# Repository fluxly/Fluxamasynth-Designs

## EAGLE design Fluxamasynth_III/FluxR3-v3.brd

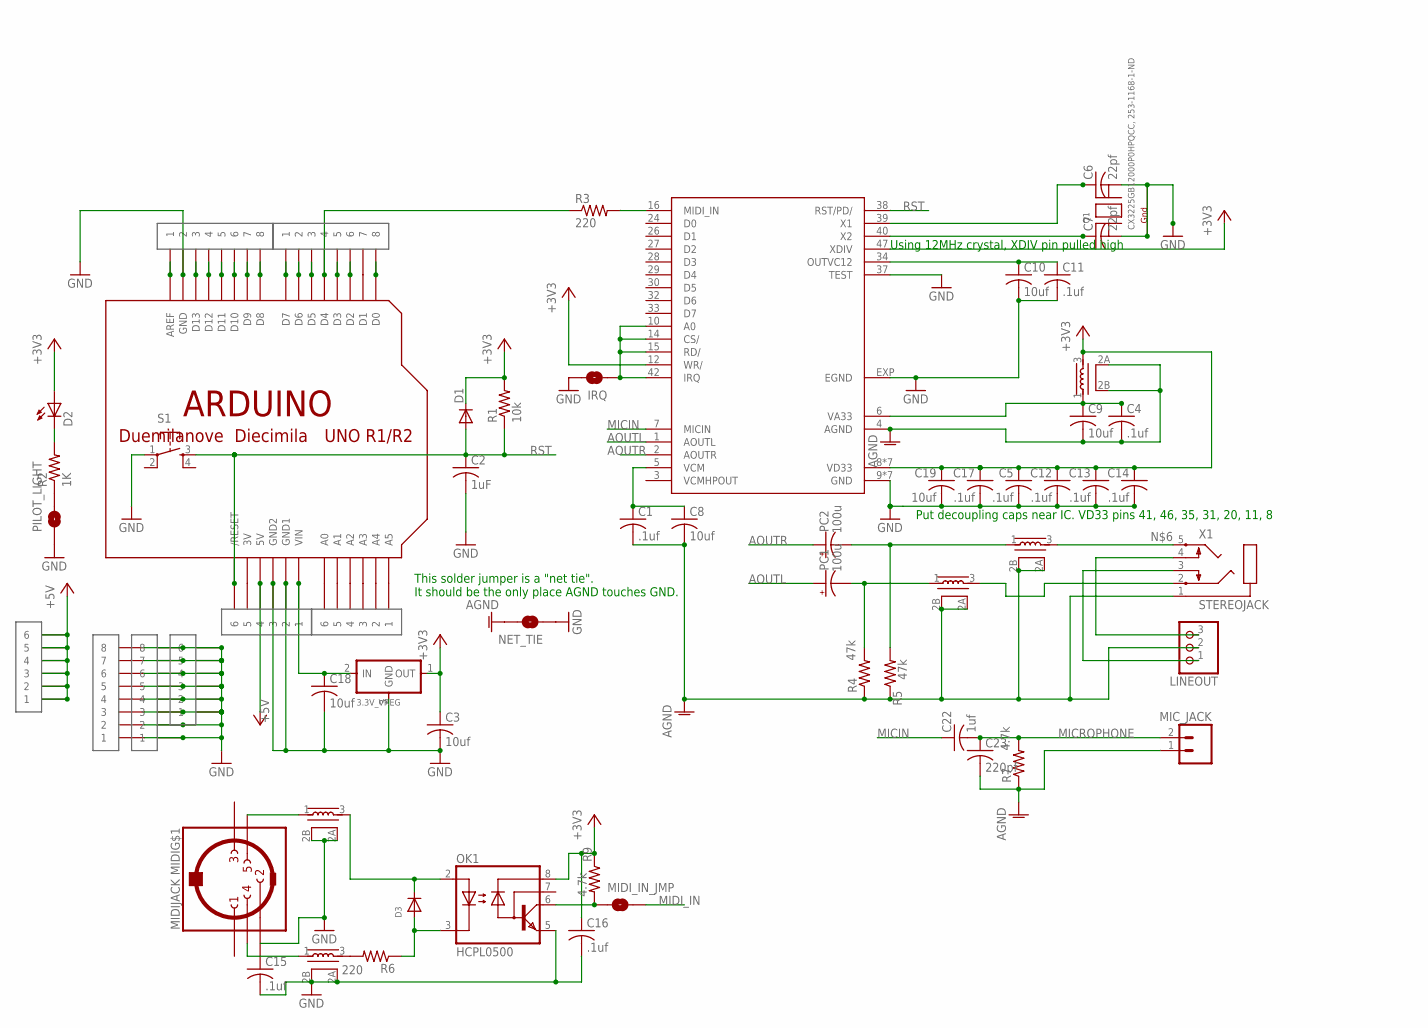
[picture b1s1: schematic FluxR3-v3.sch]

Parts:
3.3V_VREG: REGULATORSOT23; SOT23
ARDUINO: ARDUINO-NOHOLE
C1, C4, C5, C11, C12, C13, C14, C17: .1uf; C0603K
C2: 1uF; C0805
C3, C8, C9, C10, C18, C19: 10uf; C0805
C6, C7: 22pf; C0805
C15, C16: .1uf; C0805
C22: 1uf; C0805
C23: 220pf; C0805
D1: DIODESOD123; SOD123
D2: LED1206; LED-1206
D3: DIODE_SOD-523; SOD-523
IRQ: MODERNDEVICE_SOLDERJUMPERTRACE; MODERNDEVICE_SJ_2S-TRACE
LINEOUT: PINHD-1X3; 1X03
MIC_JACK: M02PTH; 1X02
MIDI: MIDIJACK; CP-2350
MIDI_IN_JMP: SOLDERJUMPERNO; SJ_2S-NO
NET_TIE: MODERNDEVICE_SOLDERJUMPERTRACE; MODERNDEVICE_SJ_2S-TRACE
OK1: HCPL0500; SOIC08
PC1, PC2: 100u; PANASONIC_E
PILOT_LIGHT: MODERNDEVICE_SOLDERJUMPERTRACE; MODERNDEVICE_SJ_2S-TRACE
Q1: CX3225GB12000P0HPQCC, 253-1168-1-ND; MODERNDEVICE_NX3225
R1: 10k; M0805
R2: 1K; M0805
R3, R6: 220; M0805
R4, R5: 47k; R0603
R7: 4.7k; M0805
R9: 4.7k; R0603
S1: 6MM_SWITCH6MM_SWITCH; 6MM_SWITCH
SAM2695: SAM2695; QFN48
U$1, U$9, U$11, U$13: 1X8_CLEAN
U$2, U$3, U$6, U$8: 1X6_CLEAN
U$4, U$5, U$7, U$10, U$12: NFM21CC223R1H3D; 3PC
X1: STEREOJACK; STX3100

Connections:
+3V3: 3.3V_VREG.1 (OUT), C3.1, C5.1, C12.1, C13.1, C14.1, C16.1, C17.1, C19.1, D1.CATHODE (C), D2.A, OK1.8 (VCC), R1.2, R9.1, SAM2695.8 (VD33), SAM2695.11 (VD33), SAM2695.12 (WR/), SAM2695.20 (VD33), SAM2695.31 (VD33), SAM2695.35 (VD33), SAM2695.41 (VD33), SAM2695.46 (VD33), SAM2695.47 (XDIV), U$7.3
+5V: ARDUINO.5V, U$2.P$1 (1), U$2.P$2 (2), U$2.P$3 (3), U$2.P$4 (4), U$2.P$5 (5), U$2.P$6 (6), U$6.P$4 (4)
A0: ARDUINO.A0, U$8.P$6 (6)
A1: ARDUINO.A1, U$8.P$5 (5)
A2: ARDUINO.A2, U$8.P$4 (4)
A3: ARDUINO.A3, U$8.P$3 (3)
A4: ARDUINO.A4, U$8.P$2 (2)
A5: ARDUINO.A5, U$8.P$1 (1)
AGND: C1.2, C4.2, C8.2, C9.2, C23.2, LINEOUT.2, MIC_JACK.1, NET_TIE.2, R4.1, R5.1, R7.1, SAM2695.4 (AGND), U$4.2A, U$4.2B, U$5.2A, U$5.2B, U$7.2A, U$7.2B, X1.1
AOUTL: PC1.+, SAM2695.1 (AOUTL)
AOUTR: PC2.+, SAM2695.2 (AOUTR)
GND: 3.3V_VREG.3 (GND), ARDUINO.GND, ARDUINO.GND1, ARDUINO.GND2, C2.2, C3.2, C5.2, C6.2, C7.2, C10.2, C11.2, C12.2, C13.2, C14.2, C15.2, C16.2, C17.2, C18.2, C19.2, IRQ.2, NET_TIE.1, OK1.5 (GND), PILOT_LIGHT.1, Q1.2 (G2), Q1.4 (G1), S1.1, SAM2695.9 (GND), SAM2695.13 (GND), SAM2695.18 (GND), SAM2695.25 (GND), SAM2695.36 (GND), SAM2695.37 (TEST), SAM2695.45 (GND), SAM2695.48 (GND), SAM2695.EXP (EGND), U$1.P$1 (1), U$1.P$2 (2), U$1.P$3 (3), U$1.P$4 (4), U$1.P$5 (5), U$1.P$6 (6), U$1.P$7 (7), U$1.P$8 (8), U$3.P$1 (1), U$3.P$2 (2), U$3.P$3 (3), U$3.P$4 (4), U$3.P$5 (5), U$3.P$6 (6), U$6.P$2 (2), U$6.P$3 (3), U$10.2A, U$10.2B, U$11.P$1 (1), U$11.P$2 (2), U$11.P$3 (3), U$11.P$4 (4), U$11.P$5 (5), U$11.P$6 (6), U$11.P$7 (7), U$11.P$8 (8), U$12.2A, U$12.2B, U$13.P$2 (2)
MICIN: C22.1, SAM2695.7 (MICIN)
MICROPHONE: C22.2, C23.1, MIC_JACK.2, R7.2
MIDI_FROM_ARDUINO: ARDUINO.D4, MIDI_IN_JMP.1, OK1.6 (VO), R3.1, R9.2, U$9.P$4 (4)
MIDI_IN: MIDI_IN_JMP.2, R3.2, SAM2695.16 (MIDI_IN)
unnamed: ARDUINO.D1, U$9.P$7 (7)
unnamed: MIDI.4, U$10.1
unnamed: IRQ.1, SAM2695.10 (A0), SAM2695.14 (CS/), SAM2695.15 (RD/), SAM2695.42 (IRQ)
unnamed: ARDUINO.3V, U$6.P$5 (5)
unnamed: PC1.-, R4.2, U$5.1
unnamed: U$4.3, X1.5
unnamed: R6.2, U$10.3
unnamed: D3.K (C), OK1.2 (A), U$12.3
unnamed: D2.C, R2.2
unnamed: C15.1, MIDI.2
unnamed: MIDI.5, U$12.1
unnamed: D3.A, OK1.3 (C), R6.1
unnamed: ARDUINO.D8, U$13.P$8 (8)
unnamed: ARDUINO.D9, U$13.P$7 (7)
unnamed: LINEOUT.3, X1.4
unnamed: ARDUINO.D11, U$13.P$5 (5)
unnamed: ARDUINO.D10, U$13.P$6 (6)
unnamed: LINEOUT.1, X1.3
unnamed: ARDUINO.D12, U$13.P$4 (4)
unnamed: ARDUINO.D13, U$13.P$3 (3)
unnamed: ARDUINO.D6, U$9.P$2 (2)
unnamed: ARDUINO.AREF, U$13.P$1 (1)
unnamed: ARDUINO.D5, U$9.P$3 (3)
unnamed: ARDUINO.D0, U$9.P$8 (8)
unnamed: ARDUINO.D2, U$9.P$6 (6)
unnamed: ARDUINO.D3, U$9.P$5 (5)
unnamed: ARDUINO.D7, U$9.P$1 (1)
unnamed: PILOT_LIGHT.2, R2.1
unnamed: C6.1, SAM2695.39 (X1)
unnamed: C7.1, SAM2695.40 (X2)
OUTVC12: C10.1, C11.1, SAM2695.34 (OUTVC12)
OUT_L: U$5.3, X1.2
OUT_R: PC2.-, R5.2, U$4.1
RST: ARDUINO.RESET (/RESET), C2.1, D1.ANODE (A), R1.1, S1.3 (S), SAM2695.38 (RST/PD/), U$6.P$6 (6)
VA33: C4.1, C9.1, SAM2695.6 (VA33), U$7.1
VCM: C1.1, C8.1, SAM2695.5 (VCM)
VIN: 3.3V_VREG.2 (IN), ARDUINO.VIN, C18.1, U$6.P$1 (1)

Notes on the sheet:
Using 12MHz crystal, XDIV pin pulled high
Put decoupling caps near IC. VD33 pins 41, 46, 35, 31, 20, 11, 8
This solder jumper is a "net tie". It should be the only place AGND touches GND.

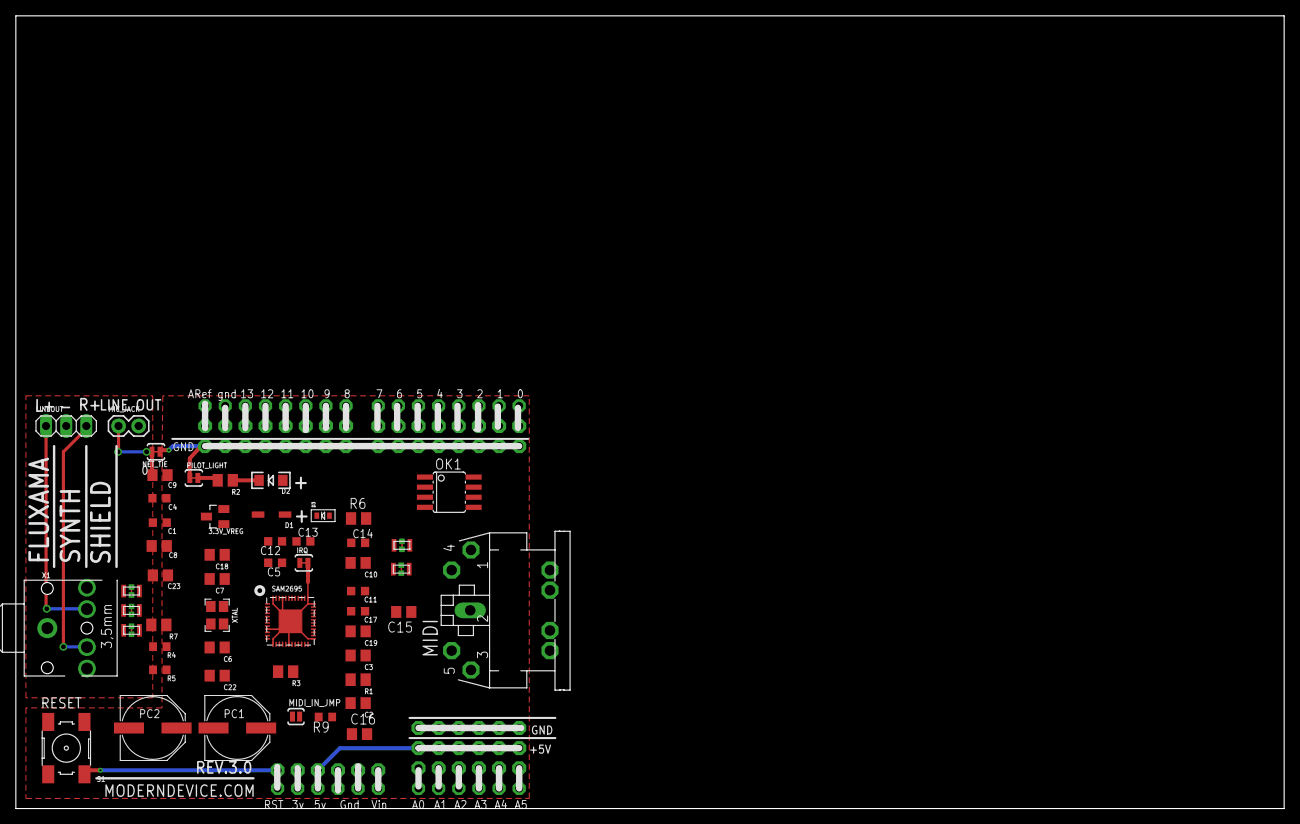
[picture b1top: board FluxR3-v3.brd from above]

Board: 2 copper layers, 160.0 x 100.0 mm, 61 parts (0 on the bottom side), 53 nets.

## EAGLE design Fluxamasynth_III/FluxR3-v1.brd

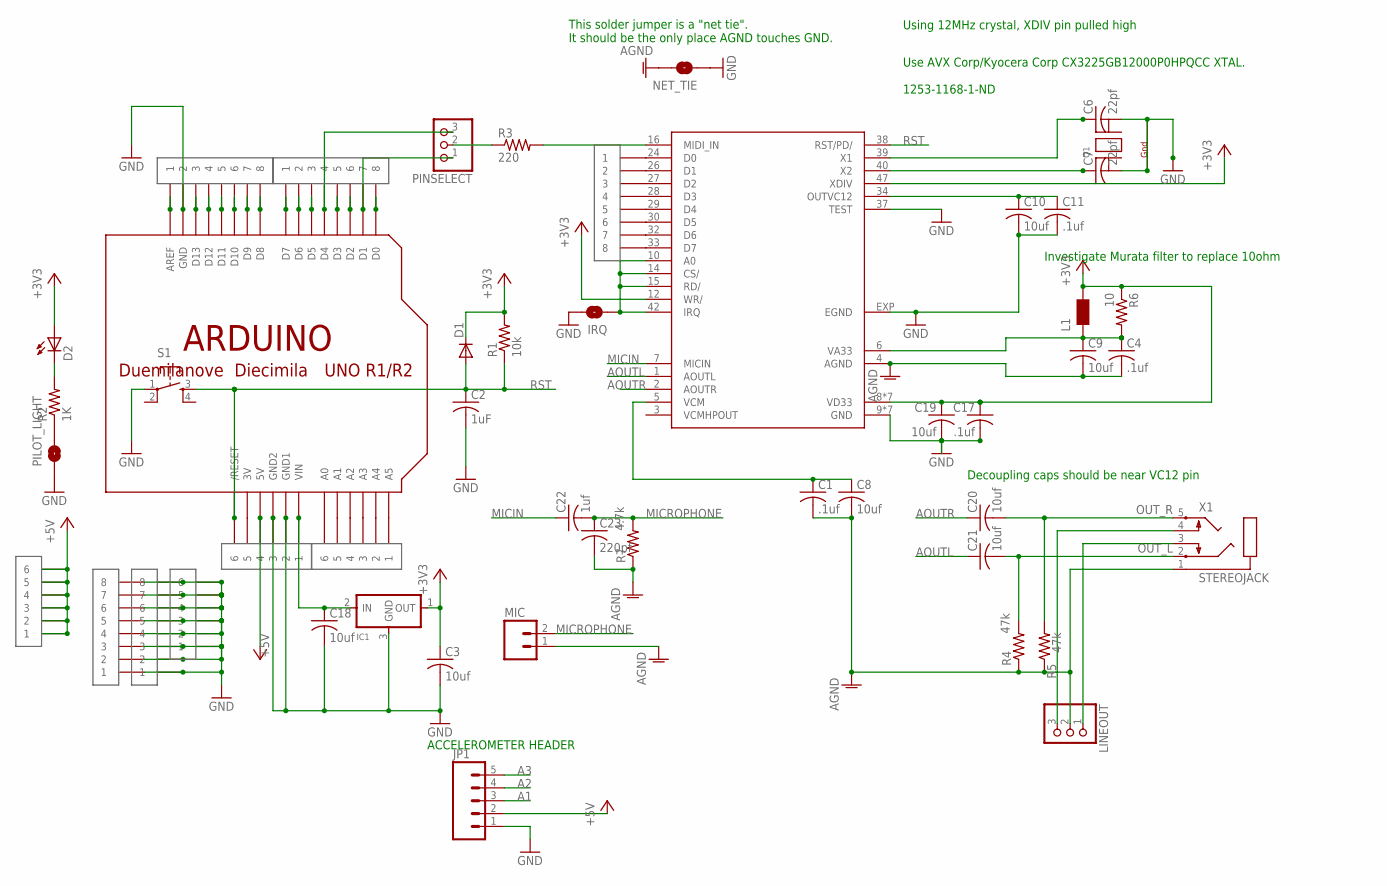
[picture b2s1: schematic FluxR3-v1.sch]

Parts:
C1, C4, C11, C17: .1uf; C0603K
C2: 1uF; C0805
C3, C8, C9, C10, C18, C19, C20, C21: 10uf; C0805
C6, C7: 22pf; C0805
C22: 1uf; C0805
C23: 220pf; C0805
D1: DIODESOD123; SOD123
D2: LED1206; LED-1206
IC1: REGULATORSOT23; SOT23
IRQ: MODERNDEVICE_SOLDERJUMPERTRACE; MODERNDEVICE_SJ_2S-TRACE
JP1: M05NOSILK; 1X05_NOSILK
L1: FERRITE_BEAD_L0603; R0603
LINEOUT: PINHD-1X3; 1X03
MIC: M02PTH; 1X02
MIDI: 1X8_CLEAN
NET_TIE: MODERNDEVICE_SOLDERJUMPERTRACE; MODERNDEVICE_SJ_2S-TRACE
PILOT_LIGHT: MODERNDEVICE_SOLDERJUMPERTRACE; MODERNDEVICE_SJ_2S-TRACE
PINSELECT: PINHD-1X3; 1X03
Q1: MODERNDEVICE_XTAL-4-3225; MODERNDEVICE_NX3225
R1: 10k; M0805
R2: 1K; M0805
R3: 220; M0805
R4, R5: 47k; R0603
R6: 10; M0805
R7: 4.7k; M0805
S1: 6MM_SWITCH6MM_SWITCH; 6MM_SWITCH
U1: SAM2695; QFN48
U$1, U$9, U$11, U$13: 1X8_CLEAN
U$2, U$3, U$6, U$8: 1X6_CLEAN
U$12: ARDUINO-NOHOLE
X1: STEREOJACK; STX3100

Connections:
+3V3: C3.1, C17.1, C19.1, D1.CATHODE (C), D2.A, IC1.1 (OUT), L1.2, R1.2, R6.1, U1.8 (VD33), U1.11 (VD33), U1.12 (WR/), U1.20 (VD33), U1.31 (VD33), U1.35 (VD33), U1.41 (VD33), U1.46 (VD33), U1.47 (XDIV)
+5V: JP1.2, U$2.P$1 (1), U$2.P$2 (2), U$2.P$3 (3), U$2.P$4 (4), U$2.P$5 (5), U$2.P$6 (6), U$6.P$4 (4), U$12.5V
A0: U$8.P$6 (6), U$12.A0
A1: JP1.3, U$8.P$5 (5), U$12.A1
A2: JP1.4, U$8.P$4 (4), U$12.A2
A3: JP1.5, U$8.P$3 (3), U$12.A3
A4: U$8.P$2 (2), U$12.A4
A5: U$8.P$1 (1), U$12.A5
AGND: C1.2, C4.2, C8.2, C9.2, C23.2, LINEOUT.2, MIC.1, NET_TIE.2, R4.1, R5.1, R7.1, U1.4 (AGND), X1.1
AOUTL: C21.1, U1.1 (AOUTL)
AOUTR: C20.1, U1.2 (AOUTR)
GND: C2.2, C3.2, C6.2, C7.2, C10.2, C11.2, C17.2, C18.2, C19.2, IC1.3 (GND), IRQ.2, JP1.1, NET_TIE.1, PILOT_LIGHT.1, Q1.2 (G2), Q1.4 (G1), S1.1, U1.9 (GND), U1.13 (GND), U1.18 (GND), U1.25 (GND), U1.36 (GND), U1.37 (TEST), U1.45 (GND), U1.48 (GND), U1.EXP (EGND), U$1.P$1 (1), U$1.P$2 (2), U$1.P$3 (3), U$1.P$4 (4), U$1.P$5 (5), U$1.P$6 (6), U$1.P$7 (7), U$1.P$8 (8), U$3.P$1 (1), U$3.P$2 (2), U$3.P$3 (3), U$3.P$4 (4), U$3.P$5 (5), U$3.P$6 (6), U$6.P$2 (2), U$6.P$3 (3), U$11.P$1 (1), U$11.P$2 (2), U$11.P$3 (3), U$11.P$4 (4), U$11.P$5 (5), U$11.P$6 (6), U$11.P$7 (7), U$11.P$8 (8), U$12.GND, U$12.GND1, U$12.GND2, U$13.P$2 (2)
MICIN: C22.1, U1.7 (MICIN)
MICROPHONE: C22.2, C23.1, MIC.2, R7.2
unnamed: PINSELECT.2, R3.1
unnamed: R3.2, U1.16 (MIDI_IN)
unnamed: IRQ.1, U1.10 (A0), U1.14 (CS/), U1.15 (RD/), U1.42 (IRQ)
unnamed: U$6.P$5 (5), U$12.3V
unnamed: MIDI.P$1 (1), U1.24 (D0)
unnamed: MIDI.P$2 (2), U1.26 (D1)
unnamed: MIDI.P$3 (3), U1.27 (D2)
unnamed: MIDI.P$4 (4), U1.28 (D3)
unnamed: D2.C, R2.2
unnamed: MIDI.P$5 (5), U1.29 (D4)
unnamed: MIDI.P$6 (6), U1.30 (D5)
unnamed: C1.1, C8.1, U1.5 (VCM)
unnamed: MIDI.P$7 (7), U1.32 (D6)
unnamed: MIDI.P$8 (8), U1.33 (D7)
unnamed: U$12.D8, U$13.P$8 (8)
unnamed: PINSELECT.1, U$9.P$7 (7), U$12.D1
unnamed: PINSELECT.3, U$9.P$4 (4), U$12.D4
unnamed: U$12.D9, U$13.P$7 (7)
unnamed: LINEOUT.3, X1.4
unnamed: U$12.D11, U$13.P$5 (5)
unnamed: U$12.D10, U$13.P$6 (6)
unnamed: LINEOUT.1, X1.3
unnamed: U$12.D12, U$13.P$4 (4)
unnamed: U$12.D13, U$13.P$3 (3)
unnamed: U$9.P$2 (2), U$12.D6
unnamed: U$12.AREF, U$13.P$1 (1)
unnamed: U$9.P$3 (3), U$12.D5
unnamed: U$9.P$8 (8), U$12.D0
unnamed: U$9.P$6 (6), U$12.D2
unnamed: U$9.P$5 (5), U$12.D3
unnamed: U$9.P$1 (1), U$12.D7
unnamed: C4.1, C9.1, L1.1, R6.2, U1.6 (VA33)
unnamed: PILOT_LIGHT.2, R2.1
unnamed: C6.1, U1.39 (X1)
unnamed: C7.1, U1.40 (X2)
OUTVC12: C10.1, C11.1, U1.34 (OUTVC12)
OUT_L: C21.2, R4.2, X1.2
OUT_R: C20.2, R5.2, X1.5
RST: C2.1, D1.ANODE (A), R1.1, S1.3 (S), U1.38 (RST/PD/), U$6.P$6 (6), U$12.RESET (/RESET)
VIN: C18.1, IC1.2 (IN), U$6.P$1 (1), U$12.VIN

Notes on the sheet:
Using 12MHz crystal, XDIV pin pulled high
Investigate Murata filter to replace 10ohm
Use AVX Corp/Kyocera Corp CX3225GB12000P0HPQCC XTAL. 1253-1168-1-ND
Decoupling caps should be near VC12 pin
This solder jumper is a "net tie". It should be the only place AGND touches GND.
ACCELEROMETER HEADER

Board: 2 copper layers, 49 parts (0 on the bottom side), 54 nets, no tracks yet.

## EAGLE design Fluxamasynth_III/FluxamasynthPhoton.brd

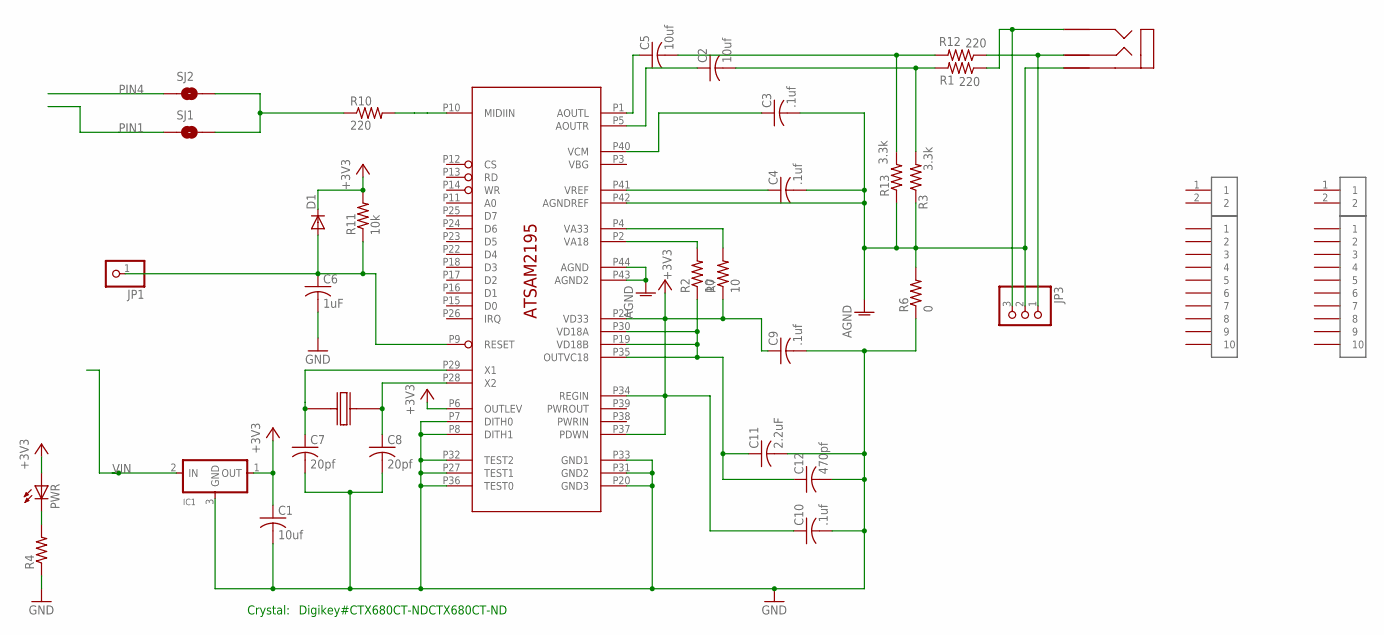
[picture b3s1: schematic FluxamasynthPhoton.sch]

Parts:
C1, C2, C5: 10uf; C0603
C3, C4, C9, C10: .1uf; C0603
C6: 1uF; C0603
C7, C8: 20pf; C0603K
C11: 2.2uF; C0603
C12: 470pf; C0603
D1: DIODESOD123; SOD123
IC1: REGULATORSOT23; SOT23
JP1: PINHD-1X1; 1X01
JP3: PINHD-1X3CB; 1X03-CLEANBIG
PWR: LED0603; LED-0603
R1, R10, R12: 220; R0603
R2, R7: 10; R0603
R3, R13: 3.3k; R0603
R4: R-US_R0603; R0603
R6: 0; R0603
R11: 10k; R0603
SJ1: SOLDERJUMPERNO; SJ_2S-NO
SJ2: SOLDERJUMPERNC2; SJ_2S-NOTRACE
U$1: ATSAM2195
U$2: CRYSTAL_7X5
U$3, U$5: 1X10_CLEAN
U$4: STEREO_AUDIO_JACK_SMT
U$6, U$7: 1X2_CLEAN

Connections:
+3V3: C1.1, C9.1, C10.1, D1.CATHODE (C), IC1.1 (OUT), PWR.A, R7.1, R11.2, U$1.P6 (OUTLEV), U$1.P21 (VD33), U$1.P34 (REGIN), U$1.P37 (PDWN)
AGND: C3.2, C4.2, JP3.2, R3.1, R6.2, R13.1, U$1.P42 (AGNDREF), U$1.P43 (AGND2), U$1.P44 (AGND), U$4.P$1 (SHIELD)
CA11: C2.1, U$1.P5 (AOUTR)
GND: C1.2, C6.2, C7.2, C8.2, C9.2, C10.2, C11.2, C12.2, IC1.3 (GND), R4.1, R6.1, U$1.P7 (DITH0), U$1.P8 (DITH1), U$1.P20 (GND3), U$1.P27 (TEST1), U$1.P31 (GND2), U$1.P32 (TEST2), U$1.P33 (GND1), U$1.P36 (TEST0)
unnamed: R10.1, SJ1.2, SJ2.2
unnamed: R10.2, U$1.P10 (MIDIIN)
unnamed: C8.1, U$1.P28 (X2), U$2.P$3
unnamed: C7.1, U$1.P29 (X1), U$2.P$1
unnamed: C11.1, C12.1, R2.1, U$1.P19 (VD18B), U$1.P30 (VD18A), U$1.P35 (OUTVC18)
unnamed: R2.2, U$1.P2 (VA18)
unnamed: C5.1, U$1.P1 (AOUTL)
unnamed: PWR.C, R4.2
unnamed: C5.2, R12.2, R13.2
unnamed: C2.2, R1.2, R3.2
unnamed: C3.1, U$1.P40 (VCM)
unnamed: R7.2, U$1.P4 (VA33)
unnamed: C6.1, D1.ANODE (A), JP1.1, R11.1, U$1.P9 (RESET)
unnamed: C4.1, U$1.P41 (VREF)
unnamed: JP3.3, R1.1, U$4.P$2 (TIP)
unnamed: JP3.1, R12.1, U$4.P$3 (RING)
PIN1: SJ1.1
PIN4: SJ2.1
VIN: IC1.2 (IN)

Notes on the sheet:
Digikey#CTX680CT-NDCTX680CT-ND
Crystal:

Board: 2 copper layers, 36 parts (1 on the bottom side), 20 nets, no tracks yet.

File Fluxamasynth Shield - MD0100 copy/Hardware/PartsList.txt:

Partlist

Exported from FluxamasynthShield.sch at 12/22/10 11:38 AM

EAGLE Version 5.10.0 Copyright (c) 1988-2010 CadSoft

Part     Value                      Device                     Package        Library             Sheet

C1       10uf                       C-USC0805                  C0805          rcl                 1
C2       2.2uF                      C-USC0805                  C0805          rcl                 1
C3       .1uf                       C-USC0805                  C0805          rcl                 1
C4       .1uf                       C-USC0805                  C0805          rcl                 1
C5       2.2uF                      C-USC0805                  C0805          rcl                 1
C6       1uF                        C-USC0805                  C0805          rcl                 1
C7       18pf                       C-USC0805                  C0805          rcl                 1
C8       18pf                       C-USC0805                  C0805          rcl                 1
C9       .1uf                       C-USC0805                  C0805          rcl                 1
C10      .1uf                       C-USC0805                  C0805          rcl                 1
C11      2.2uF                      C-USC0805                  C0805          rcl                 1
C12      470pf                      C-USC0805                  C0805          rcl                 1
D1                                  DIODESOD123                SOD123         ng                  1
IC1                                 REGULATORSOT23             SOT23          ng                  1
JP1                                 PINHD-1X3                  1X03           pinhead             1
JP3                                 PINHD-1X3                  1X03           pinhead             1
Q2       9.6MHz                     CRYSTALTC26H               TC26H          crystal             1
R1       220                        R-US_M0805                 M0805          rcl                 1
R2       10                         R-US_M0805                 M0805          rcl                 1
R3       3.3k                       R-US_M0805                 M0805          rcl                 1
R4                                  R-US_M0805                 M0805          rcl                 1
R6       0                          R-US_M0805                 M0805          rcl                 1
R7       10                         R-US_M0805                 M0805          rcl                 1
R10      220                        R-US_M0805                 M0805          rcl                 1
R11      10k                        R-US_M0805                 M0805          rcl                 1
R12      220                        R-US_M0805                 M0805          rcl                 1
R13      3.3k                       R-US_M0805                 M0805          rcl                 1
S1                                  6MM_SWITCH6MM_SWITCH       6MM_SWITCH     ng                  1
U$1      ATSAM2195                  ATSAM2195                  ATSAM2195      ATSAM2195           1
U$2      ARDUINODUEMILANOVE-NOHOLES ARDUINODUEMILANOVE-NOHOLES ARDUINO-NOHOLE adafruit            1
U$3                                 LED1206                    1206           ng                  1
U$4      1X6HEADER                  1X6HEADER                  1X6HEADER      ModernDeviceHeaders 1
U$5      1X6HEADER                  1X6HEADER                  1X6HEADER      ModernDeviceHeaders 1
U$6      1X8HEADER                  1X8HEADER                  1X8HEADER      ModernDeviceHeaders 1
U$7      1X8HEADER                  1X8HEADER                  1X8HEADER      ModernDeviceHeaders 1
U$8      1X6HEADER                  1X6HEADER                  1X6HEADER      ModernDeviceHeaders 1
U$9      1X6HEADER                  1X6HEADER                  1X6HEADER      ModernDeviceHeaders 1
U$10     1X8HEADER                  1X8HEADER                  1X8HEADER      ModernDeviceHeaders 1
U$11     1X8HEADER                  1X8HEADER                  1X8HEADER      ModernDeviceHeaders 1
U$12     1X6HEADER                  1X6HEADER                  1X6HEADER      ModernDeviceHeaders 1
U$13     1X6HEADER                  1X6HEADER                  1X6HEADER      ModernDeviceHeaders 1
X1       STEREOJACK                 STEREOJACK                 STX3100        adafruit            1

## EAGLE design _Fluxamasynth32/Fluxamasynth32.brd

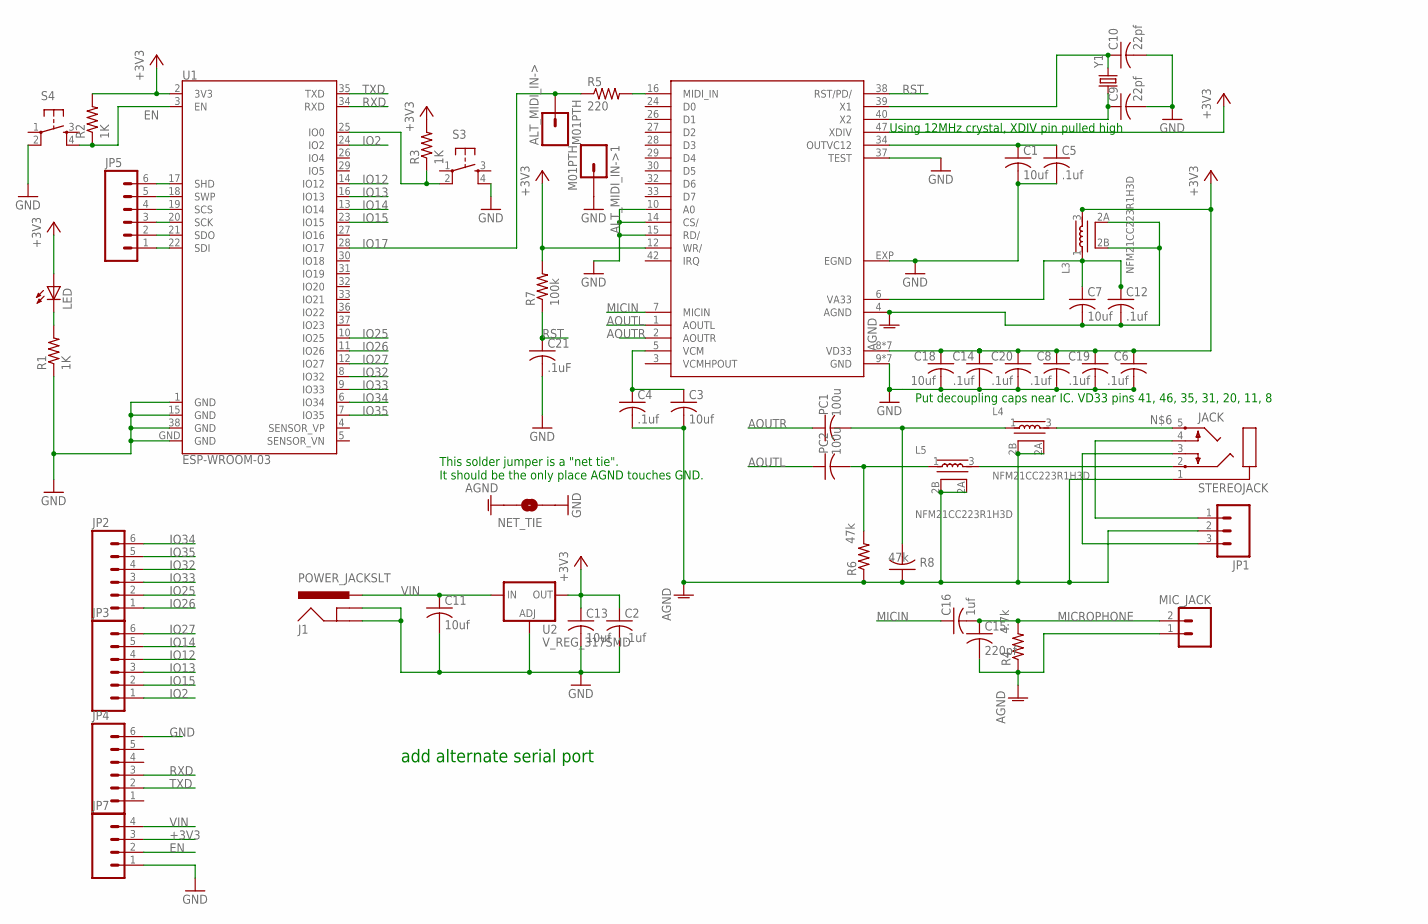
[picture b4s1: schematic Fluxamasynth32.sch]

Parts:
ALT_MIDI_IN->, ALT_MIDI_IN->1: M01PTH; 1X01
C1, C3, C7: 10uf; C0805K
C2, C4, C5, C6, C8, C12, C14, C19, C20: .1uf; C0603K
C9, C10: 22pf; C0603
C11, C13: 10uf; C1206
C15: 220pf; C0805K
C16: 1uf; C0603K
C18: 10uf; C0603K
C21: .1uF; C0603K
J1: POWER_JACKSLT; POWER_JACK_SLOT
JACK: STEREOJACK; STX3100
JP1: M03PTH; 1X03
JP2, JP3, JP4, JP5: M06NO_SILK; 1X06_NO_SILK
JP7: M041X04_NO_SILK; 1X04_NO_SILK
L3, L4, L5: NFM21CC223R1H3D; 3PC
LED: LED0603; LED-0603
MIC_JACK: M02PTH; 1X02
NET_TIE: MODERNDEVICE_SOLDERJUMPERTRACE; MODERNDEVICE_SJ_2S-TRACE
PC1, PC2: 100u; C1206K
R1, R2, R3: 1K; R0603
R4: 4.7k; R0603
R5: 220; R0603
R6: 47k; R0603
R7: 100k; R0603
R8: 47k; C0603K
S3, S4: 6MM_SWITCH6MM_SWITCH; 6MM_SWITCH
SAM2695: SAM2695; QFN48
U1: ESP-WROOM-03
U2: V_REG_317SMD; SOT223
Y1: CRYSTALTXC-7A; CRYSTAL-TXC-7A

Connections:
+3V3: C2.1, C6.1, C8.1, C13.1, C14.1, C18.1, C19.1, C20.1, JP7.3, L3.3, LED.A, R2.2, R3.2, R7.2, SAM2695.8 (VD33), SAM2695.11 (VD33), SAM2695.12 (WR/), SAM2695.20 (VD33), SAM2695.31 (VD33), SAM2695.35 (VD33), SAM2695.41 (VD33), SAM2695.46 (VD33), SAM2695.47 (XDIV), U1.2 (3V3), U2.2 (OUT), U2.4 (OUT)
AGND: C3.2, C4.2, C7.2, C12.2, C15.2, JACK.1, JP1.2, L3.2A, L3.2B, L4.2A, L4.2B, L5.2A, L5.2B, MIC_JACK.1, NET_TIE.2, R4.1, R6.1, R8.1, SAM2695.4 (AGND)
AOUTL: PC2.1, SAM2695.1 (AOUTL)
AOUTR: PC1.1, SAM2695.2 (AOUTR)
EN: JP7.2, R2.1, S4.4 (S1), U1.3 (EN)
GND: ALT_MIDI_IN->1.1, C1.2, C2.2, C5.2, C6.2, C8.2, C9.2, C10.2, C11.2, C13.2, C14.2, C18.2, C19.2, C20.2, C21.2, J1.GND@1 (GNDBREAK), J1.GND@2 (GND), JP4.6, JP7.1, NET_TIE.1, R1.1, S3.4 (S1), S4.2 (P1), SAM2695.9 (GND), SAM2695.10 (A0), SAM2695.13 (GND), SAM2695.14 (CS/), SAM2695.15 (RD/), SAM2695.18 (GND), SAM2695.25 (GND), SAM2695.36 (GND), SAM2695.37 (TEST), SAM2695.45 (GND), SAM2695.48 (GND), SAM2695.EXP (EGND), U1.1 (GND), U1.15 (GND), U1.38 (GND), U1.GND, U2.1 (ADJ)
IO2: JP3.1, U1.24 (IO2)
IO12: JP3.4, U1.14 (IO12)
IO13: JP3.3, U1.16 (IO13)
IO14: JP3.5, U1.13 (IO14)
IO15: JP3.2, U1.23 (IO15)
IO17: ALT_MIDI_IN->.1, R5.1, U1.28 (IO17)
IO25: JP2.2, U1.10 (IO25)
IO26: JP2.1, U1.11 (IO26)
IO27: JP3.6, U1.12 (IO27)
IO32: JP2.4, U1.8 (IO32)
IO33: JP2.3, U1.9 (IO33)
IO34: JP2.6, U1.6 (IO34)
IO35: JP2.5, U1.7 (IO35)
MICIN: C16.1, SAM2695.7 (MICIN)
MICROPHONE: C15.1, C16.2, MIC_JACK.2, R4.2
unnamed: R3.1, S3.2 (P1), U1.25 (IO0)
unnamed: JP5.1, U1.22 (SDI)
unnamed: L5.1, PC2.2, R6.2
unnamed: JACK.5, L4.3
unnamed: JP5.2, U1.21 (SDO)
unnamed: JP5.3, U1.20 (SCK)
unnamed: LED.C, R1.2
unnamed: JP5.4, U1.19 (SCS)
unnamed: JP5.5, U1.18 (SWP)
unnamed: R5.2, SAM2695.16 (MIDI_IN)
unnamed: JP5.6, U1.17 (SHD)
unnamed: JACK.4, JP1.1
unnamed: JACK.3, JP1.3
OUTVC12: C1.1, C5.1, SAM2695.34 (OUTVC12)
OUT_L: JACK.2, L5.3
OUT_R: L4.1, PC1.2, R8.2
RST: C21.1, R7.1, SAM2695.38 (RST/PD/)
RXD: JP4.3, U1.34 (RXD)
TXD: JP4.2, U1.35 (TXD)
VA33: C7.1, C12.1, L3.1, SAM2695.6 (VA33)
VCM: C3.1, C4.1, SAM2695.5 (VCM)
VIN: C11.1, J1.PWR, JP7.4, U2.3 (IN)
XTL1: C10.1, SAM2695.39 (X1), Y1.P$2 (2)
XTL2: C9.1, SAM2695.40 (X2), Y1.P$1 (1)

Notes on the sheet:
Using 12MHz crystal, XDIV pin pulled high
Put decoupling caps near IC. VD33 pins 41, 46, 35, 31, 20, 11, 8
This solder jumper is a "net tie". It should be the only place AGND touches GND.
add alternate serial port

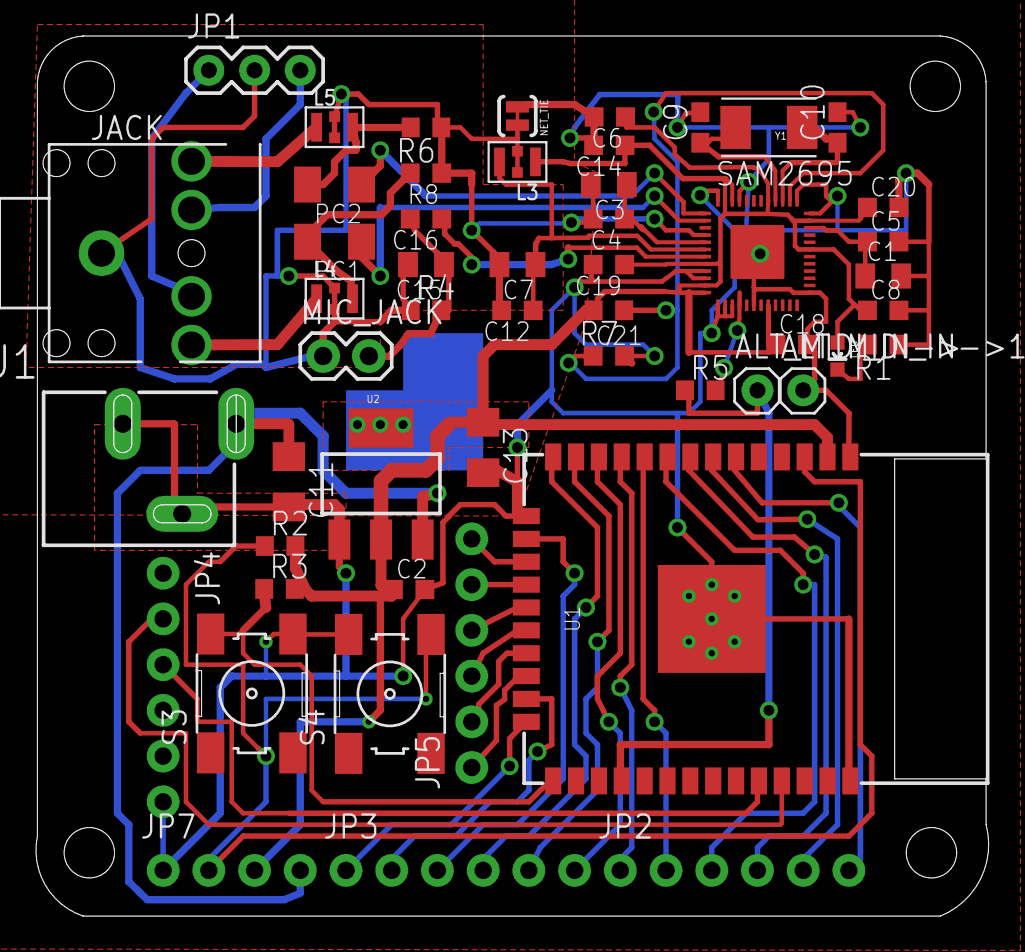
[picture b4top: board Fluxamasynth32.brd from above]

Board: 2 copper layers, 52.9 x 48.9 mm, 52 parts (0 on the bottom side), 45 nets.

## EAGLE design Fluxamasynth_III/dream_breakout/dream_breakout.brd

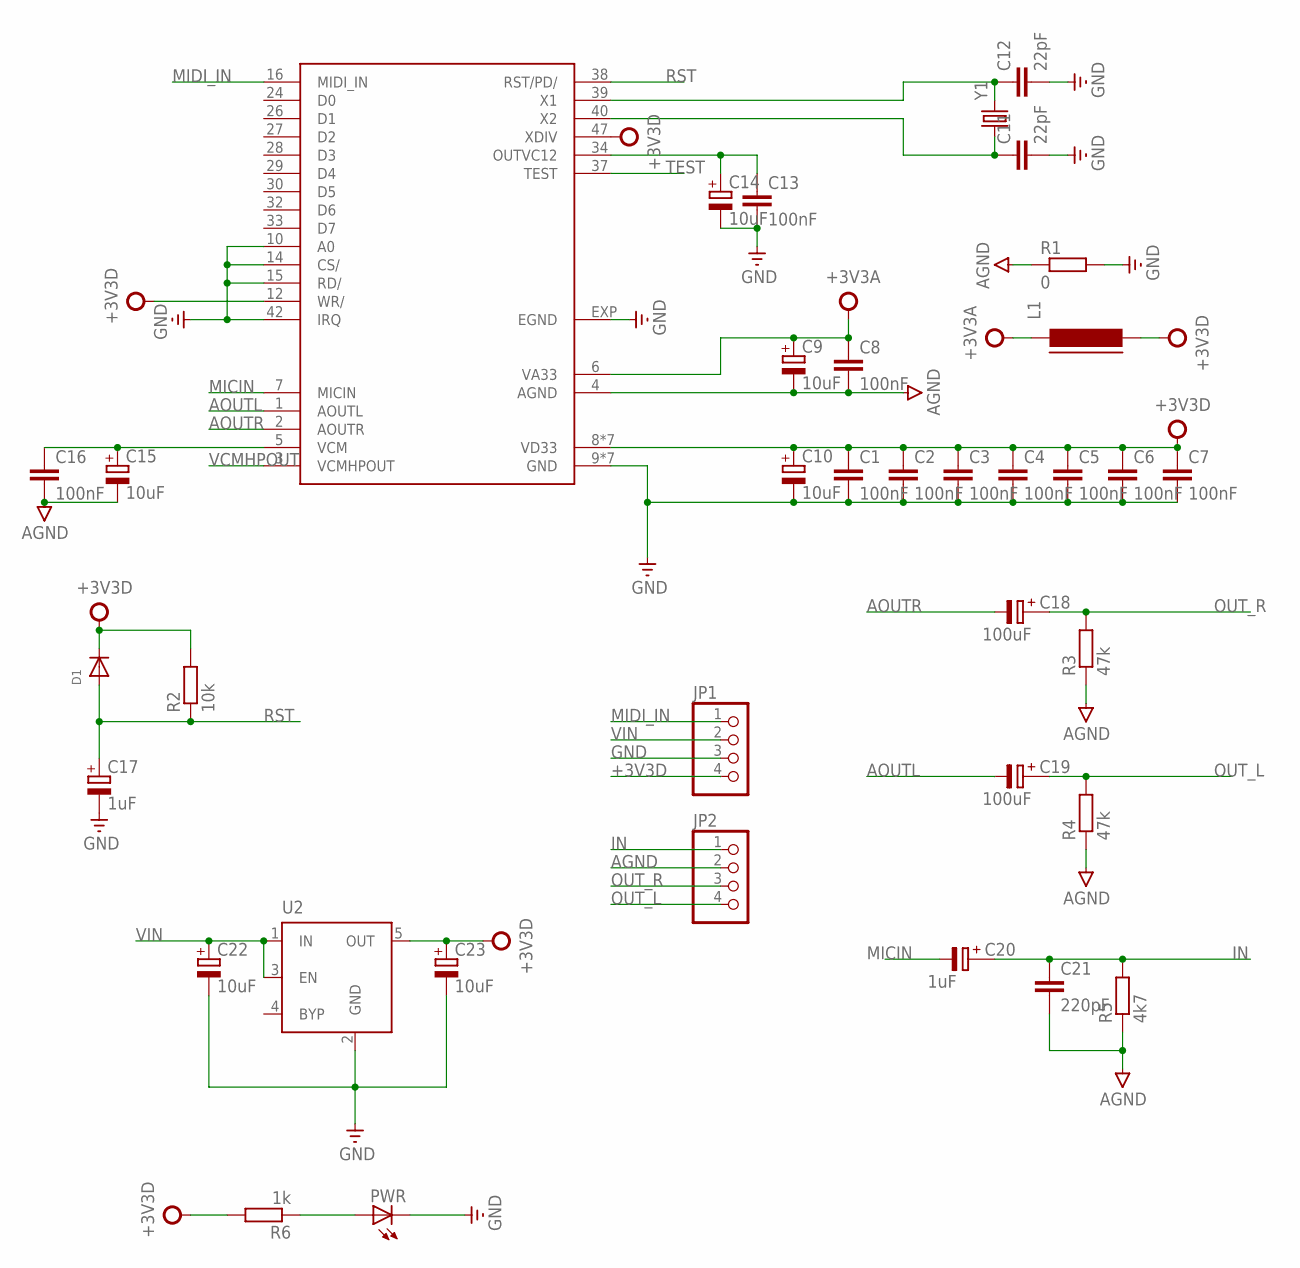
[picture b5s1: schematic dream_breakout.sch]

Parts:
C1, C2, C3, C4, C5, C6, C7, C8, C13, C16: 100nF; C0603K
C9, C10, C14, C15, C22, C23: 10uF; A/3216-18R
C11, C12: 22pF; C0603K
C17: 1uF; A/3216-18R
C18, C19: 100uF; SV-B
C20: 1uF; SV-B
C21: 220pF; C0603K
D1: DIODESOD-123; SOD-123
JP1, JP2: HEADER-1X4ROUND; 1X04_ROUND
L1: FERRITE-0603; FB603
PWR: LEDCHIP-LED0603; CHIP-LED0603
R1: 0; R0603
R2: 10k; R0603
R3, R4: 47k; R0603
R5: 4k7; R0603
R6: 1k; R0603
U1: SAM2695; QFN48
U2: MIC5219XX; SOT23-5
Y1: CRYSTALTXC-7A; CRYSTAL-TXC-7A

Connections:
+3V3A: C8.1, C9.+, L1.1, U1.6 (VA33)
+3V3D: C1.1, C2.1, C3.1, C4.1, C5.1, C6.1, C7.1, C10.+, C23.+, D1.C, JP1.4, L1.2, R2.2, R6.2, U1.8 (VD33), U1.11 (VD33), U1.12 (WR/), U1.20 (VD33), U1.31 (VD33), U1.35 (VD33), U1.41 (VD33), U1.46 (VD33), U1.47 (XDIV), U2.5 (OUT)
AGND: C8.2, C9.-, C15.-, C16.2, C21.2, JP2.2, R1.1, R3.1, R4.1, R5.1, U1.4 (AGND)
AOUTL: C19.-, U1.1 (AOUTL)
AOUTR: C18.-, U1.2 (AOUTR)
GND: C1.2, C2.2, C3.2, C4.2, C5.2, C6.2, C7.2, C10.-, C11.2, C12.2, C13.2, C14.-, C17.-, C22.-, C23.-, JP1.3, PWR.C, R1.2, U1.9 (GND), U1.10 (A0), U1.13 (GND), U1.14 (CS/), U1.15 (RD/), U1.18 (GND), U1.25 (GND), U1.36 (GND), U1.42 (IRQ), U1.45 (GND), U1.48 (GND), U1.EXP (EGND), U2.2 (GND)
IN: C20.+, C21.1, JP2.1, R5.2
MICIN: C20.-, U1.7 (MICIN)
MIDI_IN: JP1.1, U1.16 (MIDI_IN)
unnamed: C13.1, C14.+, U1.34 (OUTVC12)
unnamed: C12.1, U1.39 (X1), Y1.P$2 (2)
unnamed: C11.1, U1.40 (X2), Y1.P$1 (1)
unnamed: PWR.A, R6.1
unnamed: C15.+, C16.1, U1.5 (VCM)
OUT_L: C19.+, JP2.4, R4.2
OUT_R: C18.+, JP2.3, R3.2
RST: C17.+, D1.A, R2.1, U1.38 (RST/PD/)
TEST: U1.37 (TEST)
VCMHPOUT: U1.3 (VCMHPOUT)
VIN: C22.+, JP1.2, U2.1 (IN), U2.3 (EN)

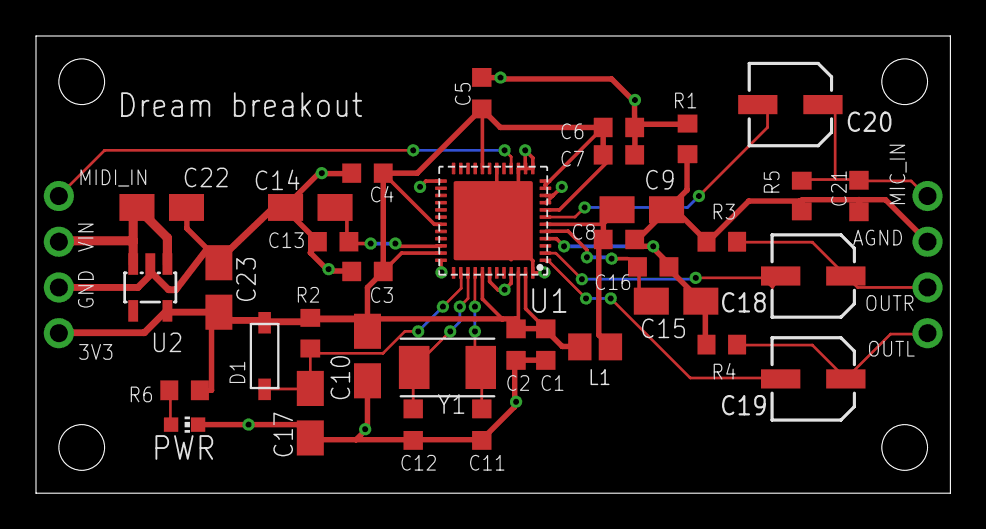
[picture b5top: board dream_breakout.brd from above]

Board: 2 copper layers, 50.8 x 25.4 mm, 38 parts (1 on the bottom side), 18 nets.

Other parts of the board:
U$1: PANDA

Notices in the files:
parts and their libraries:
SparkFun-FreqCtrl: Licensing: Creative Commons ShareAlike 4.0 International - https://creativecommons.org/licenses/by-sa/4.0
microbuilder: This work is placed in the public domain, and may be freely used for commercial and non-commercial work with the following conditions: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
